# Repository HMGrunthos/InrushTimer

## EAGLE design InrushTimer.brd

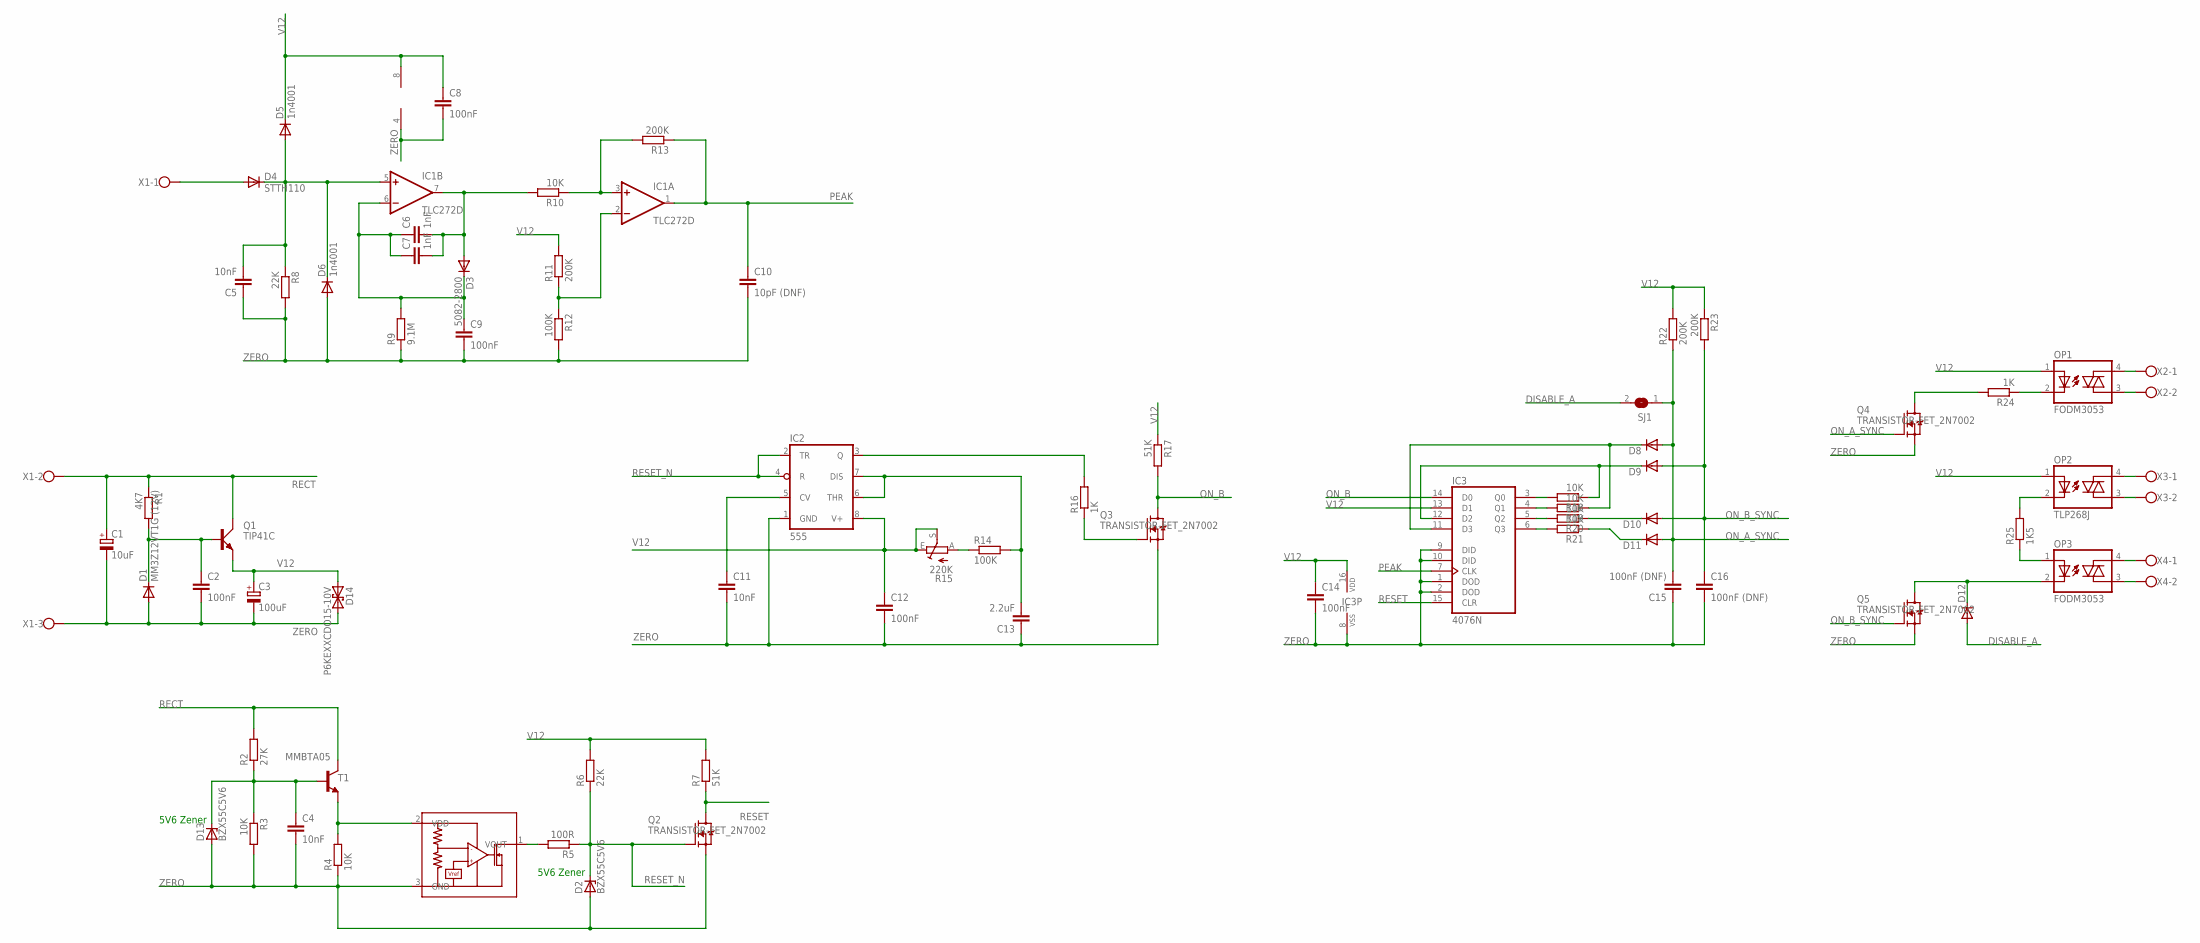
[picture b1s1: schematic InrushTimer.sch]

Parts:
C1: 10uF; E2-5
C2, C12, C14: 100nF; C050-024X044
C3: 100uF; E2,5-7
C4, C11: 10nF; C050-024X044
C5: 10nF; C0805K
C6, C7: 1nF; C0805K
C8: 100nF; C0805
C9: 100nF; C1206K
C10: 10pF (DNF); C0805K
C13: 2.2uF; C1206K
C15, C16: 100nF (DNF); C1206K
D1: MM3Z12VT1G (12V); SOD323-R
D2, D13: BZX55C5V6; DO34Z7
D3: 5082-2800; DO34-7
D4: STTH110; DO41-7.6
D5: 1n4001; DO41-10VN
D6: 1n4001; DO41-7.6
D8: 1N4148DO35-10; DO35-10
D9, D10, D11, D12: 1N4148DO35-7; DO35-7
D14: P6KEXXCDO15-10V; DO15-10V
IC1: TLC272D; SO08
IC2: 555; SO08-555
IC3: 4076N; DIL16
OP1, OP3: FODM3053; FODM
OP2: TLP268J; TLP26*
Q1: TIP41C; TO220AV
Q2, Q3, Q4, Q5: TRANSISTOR-FET_2N7002; TRANSISTOR-FET_SOT23
R1: 4K7; 0207/2V
R2: 27K; 0207/7
R3: 10K; 0207/2V
R4, R18, R19, R20, R21: 10K; R0805
R5: 100R; 0207/7
R6, R8: 22K; 0207/2V
R7, R17: 51K; 0207/2V
R9: 9.1M; 0207/7
R10: 10K; 0207/10
R11, R13, R22: 200K; 0207/2V
R12, R14: 100K; 0207/2V
R15: 220K; CA6H
R16: 1K; R0402
R23: 200K; 0207/7
R24: 1K; 0207/7
R25: 1K5; 0207/2V
SJ1: SJ
T1: MMBTA05; SOT23-BEC
U1: ROHM_BY_ELEMENT14_BATCH_1_BU48XXG; ROHM_BY_ELEMENT14_BATCH_1_SOT95P280X125-5N
X1: W237-103
X2, X3, X4: W237-102

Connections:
DISABLE_A: D12.A, SJ1.2
unnamed: D4.A, X1.1
unnamed: R14.1, R15.A
unnamed: IC3.6 (Q3), R21.2
unnamed: OP3.4 (A2), X4.1
unnamed: OP1.3 (A1), X2.2
unnamed: D12.C, OP3.2 (C), Q5.3 (D)
unnamed: C6.2, C7.2, D3.A, IC1.7 (OUT), R10.2
unnamed: C2.1, D1.C, Q1.B, R1.2
unnamed: C6.1, C7.1, C9.1, D3.C, IC1.6 (-IN), R9.2
unnamed: OP1.4 (A2), X2.1
unnamed: C5.2, D4.C, D5.A, D6.C, IC1.5 (+IN), R8.1
unnamed: OP3.3 (A1), X4.2
unnamed: R4.2, T1.E, U1.2 (VDD)
unnamed: C4.1, D13.C, R2.1, R3.1, T1.B
unnamed: OP3.1 (A), R25.1
unnamed: D9.C, IC3.12 (D2), R18.1
unnamed: OP2.2 (C), R25.2
unnamed: OP1.2 (C), R24.1
unnamed: IC3.5 (Q2), R20.2
unnamed: OP2.4 (A2), X3.1
unnamed: OP2.3 (A1), X3.2
unnamed: D8.C, IC3.11 (D3), R19.1
unnamed: R5.2, U1.1 (VOUT)
unnamed: D11.C, R21.1
unnamed: IC3.4 (Q1), R19.2
unnamed: IC1.3 (+IN), R10.1, R13.2
unnamed: C13.2, IC2.6 (THR), IC2.7 (DIS), R14.2
unnamed: D10.C, R20.1
unnamed: Q4.3 (D), R24.2
unnamed: IC3.3 (Q0), R18.2
unnamed: Q3.1 (G), R16.1
unnamed: C11.1, IC2.5 (CV)
unnamed: IC2.3 (Q), R16.2
ON_A_SYNC: C15.2, D8.A, D11.A, Q4.1 (G), R22.1, SJ1.1
ON_B: IC3.14 (D0), Q3.3 (D), R17.2
ON_B_SYNC: C16.1, D9.A, D10.A, Q5.1 (G), R23.2
PEAK: C10.1, IC1.1 (OUT), IC3.7 (CLK), R13.1
RECT: C1.+, Q1.C, R1.1, R2.2, T1.C, X1.2
RESET: IC3.15 (CLR), Q2.3 (D), R7.1
RESET_N: D2.C, IC2.2 (TR), IC2.4 (R), Q2.1 (G), R5.1, R6.1
THRESH: IC1.2 (-IN), R11.1, R12.1
V12: C3.+, C8.1, C12.1, C14.1, D5.C, D14.A (1), IC1.8 (V+), IC2.8 (V+), IC3.13 (D1), IC3.16 (VDD), OP1.1 (A), OP2.1 (A), Q1.E, R6.2, R7.2, R11.2, R15.E, R15.S, R17.1, R22.2, R23.1
ZERO: C1.-, C2.2, C3.-, C4.2, C5.1, C8.2, C9.2, C10.2, C11.2, C12.2, C13.1, C14.2, C15.1, C16.2, D1.A, D2.A, D6.A, D13.A, D14.C (2), IC1.4 (V-), IC2.1 (GND), IC3.1 (DOD), IC3.2 (DOD), IC3.8 (VSS), IC3.9 (DID), IC3.10 (DID), Q2.2 (S), Q3.2 (S), Q4.2 (S), Q5.2 (S), R3.2, R4.1, R8.2, R9.1, R12.2, U1.3 (GND), X1.3

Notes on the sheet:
5V6 Zener

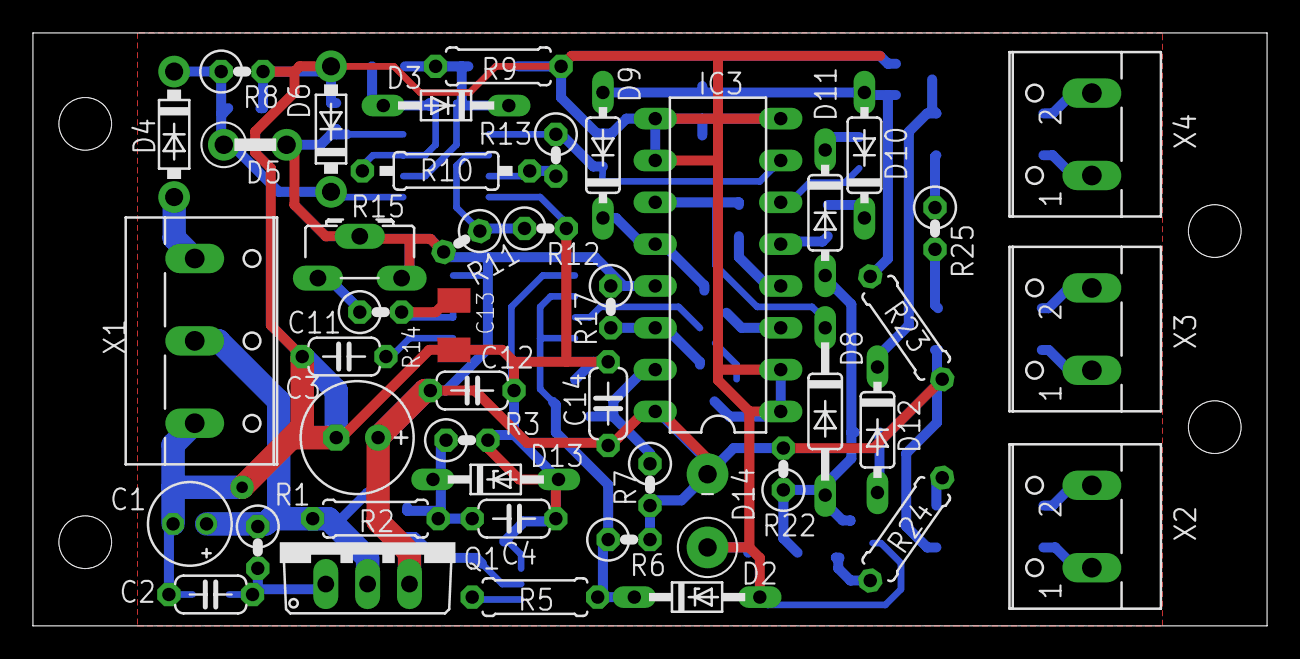
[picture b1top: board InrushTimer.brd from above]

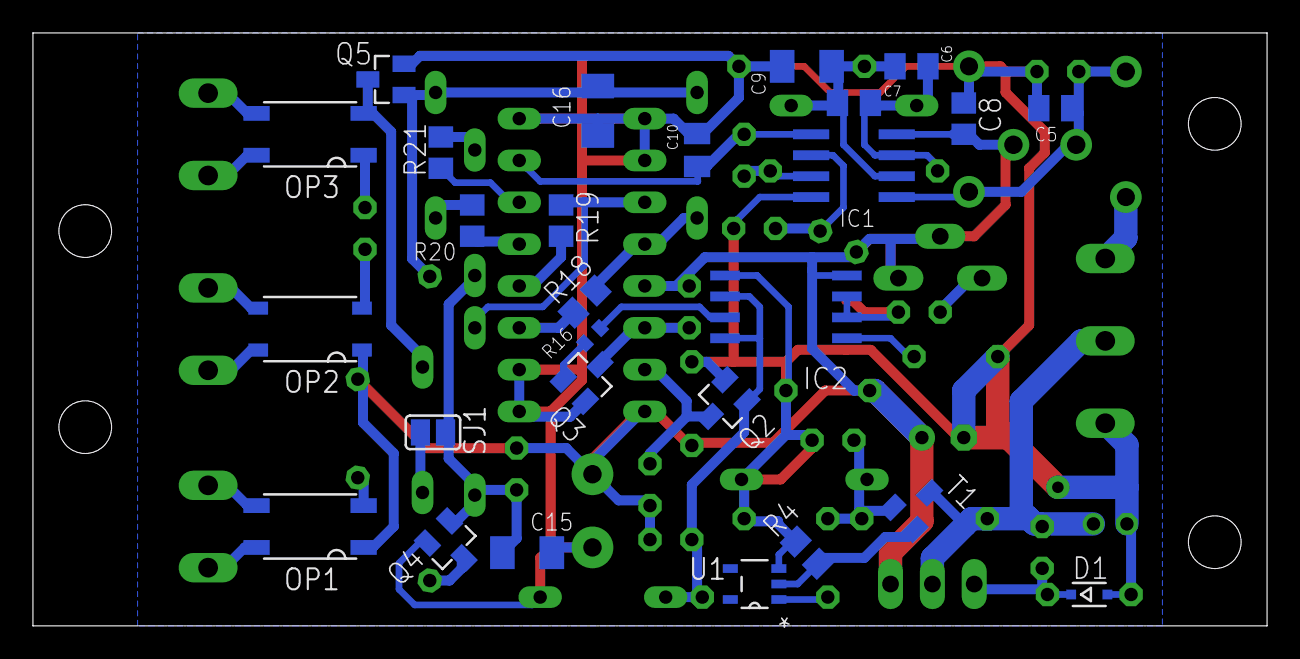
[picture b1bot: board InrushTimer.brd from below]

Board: 2 copper layers, 74.9 x 36.0 mm, 72 parts (27 on the bottom side), 44 nets.

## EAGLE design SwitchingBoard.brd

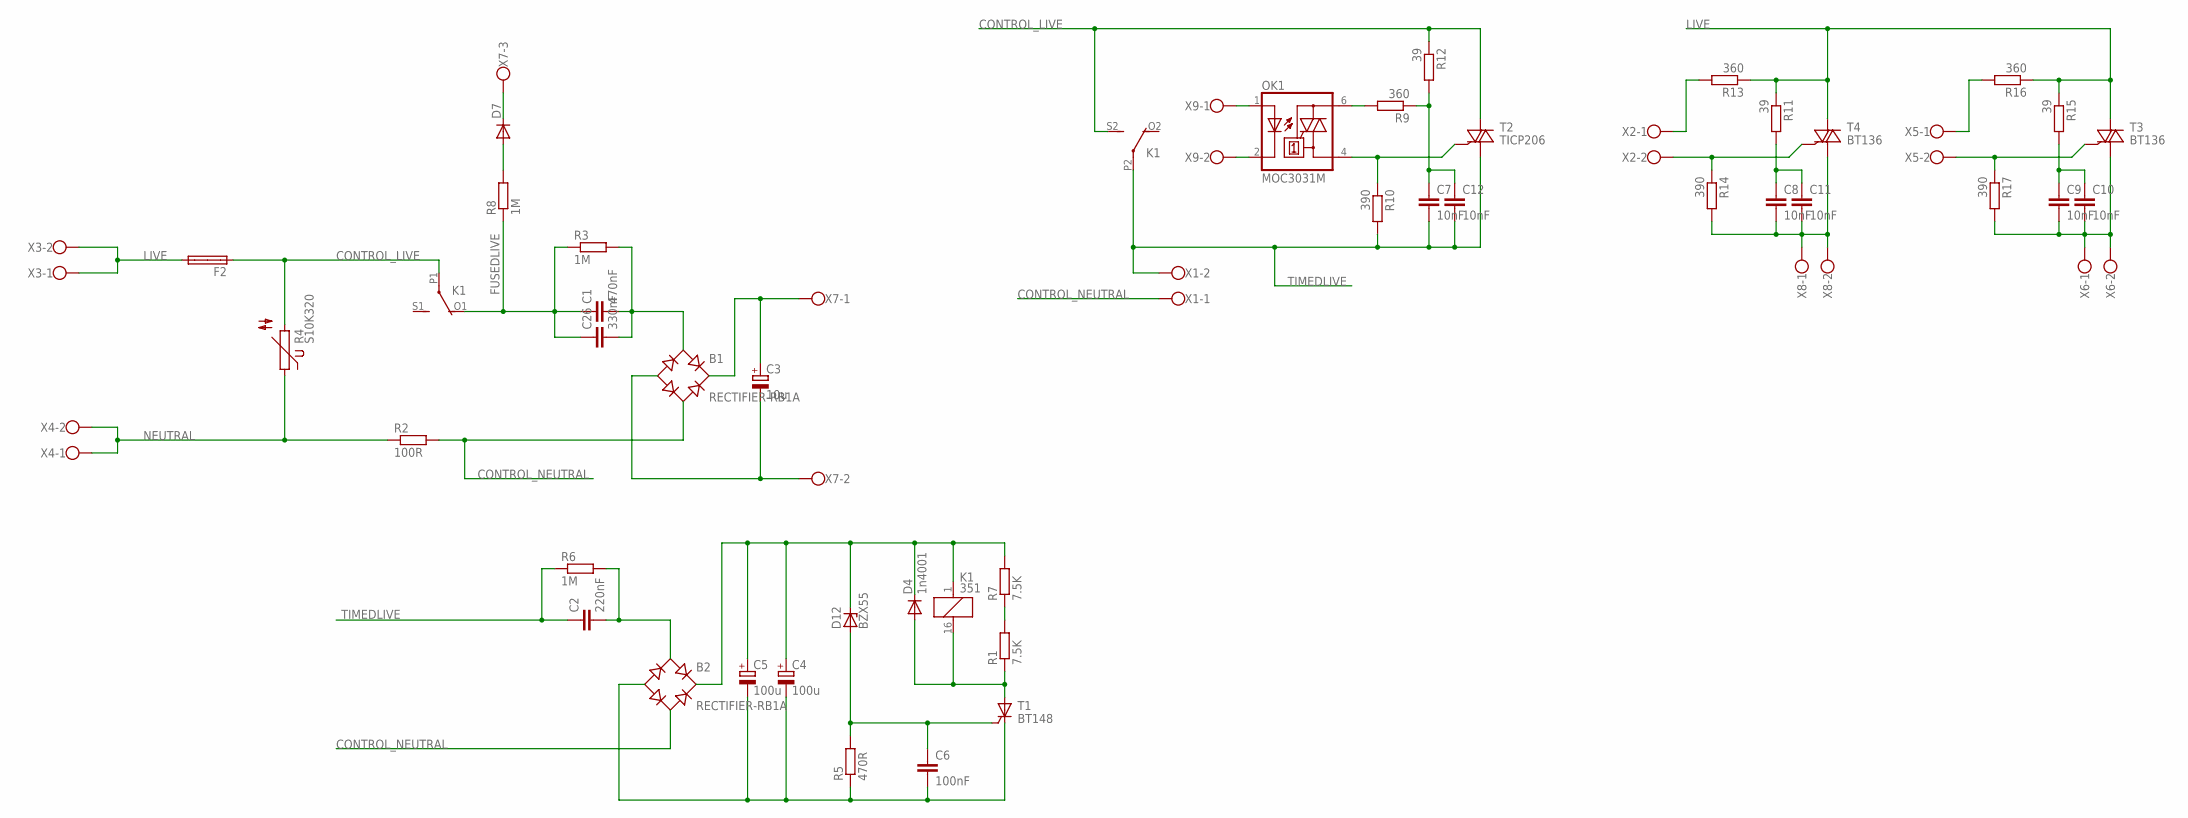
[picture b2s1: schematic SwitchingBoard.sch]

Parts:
B1, B2: RECTIFIER-RB1A; RB1A
C1: 470nF; C225-108X268
C2: 220nF; C225-062X268
C3: 10u; E2-5
C4, C5: 100u; E2,5-7
C6: 100nF; C050-024X044
C7, C8, C9: 10nF; C150-054X183
C10, C11, C12: 10nF; C102-043X133
C26: 330nF; C150-091X182
D4: 1n4001; DO41-10
D7: DIODE-DO41-10; DO41-10
D12: BZX55; DO35Z10
F2: SHKOG
K1: 351
OK1: MOC3031M; DIL06
R1, R7: 7.5K; 0207/7
R2: 100R; 0617/22
R3, R6, R8: 1M; 0617/22
R4: S10K320
R5: 470R; 0207/7
R9, R13, R16: 360; 0207/7
R10, R14, R17: 390; 0207/7
R11, R12, R15: 39; 0207/7
T1: BT148; SOT82S
T2: TICP206; TO92-6
T3, T4: BT136; TO220AB
X1, X2, X3, X4, X5, X6, X8, X9: W237-102
X7: W237-103

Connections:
CONTROL_LIVE: F2.1A, K1.P1, K1.S2 (S), R4.2, R12.1, T2.A2
CONTROL_NEUTRAL: B1.AC2, B2.AC2, R2.2, X1.1
FUSEDLIVE: C1.1, C26.1, K1.O1 (O), R3.1, R8.1
LIVE: F2.2A, R11.1, R13.1, R15.1, R16.1, T3.2 (A2), T4.2 (A2), X3.1, X3.2
unnamed: D7.A, R8.2
unnamed: B2.AC1, C2.2, R6.2
unnamed: R1.2, R7.1
unnamed: B1.AC1, C1.2, C26.2, R3.2
unnamed: D7.C, X7.3
unnamed: D4.A, K1.16 (2), R1.1, T1.A
unnamed: C6.1, D12.A, R5.2, T1.G
unnamed: C8.2, C11.2, R14.2, T4.1 (A1), X8.1, X8.2
unnamed: OK1.6 (A2), R9.2
unnamed: OK1.1 (A), X9.1
unnamed: C9.2, C10.2, R17.2, T3.1 (A1), X6.1, X6.2
unnamed: OK1.2 (C), X9.2
unnamed: OK1.4 (A1), R10.1, T2.G
unnamed: C7.1, C12.1, R9.1, R12.2
unnamed: R13.2, X2.1
unnamed: C8.1, C11.1, R11.2
unnamed: R14.1, T4.3 (G), X2.2
unnamed: C9.1, C10.1, R15.2
unnamed: R16.2, X5.1
unnamed: R17.1, T3.3 (G), X5.2
NEUTRAL: R2.1, R4.1, X4.1, X4.2
RECT: B1.+, C3.+, X7.1
RECTRELAY: B2.+, C4.+, C5.+, D4.C, D12.C, K1.1, R7.2
TIMEDLIVE: C2.1, C7.2, C12.2, K1.P2, R6.1, R10.2, T2.A1, X1.2
ZERO: B1.-, C3.-, X7.2
ZERO1: B2.-, C4.-, C5.-, C6.2, R5.1, T1.C

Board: 2 copper layers, 51 parts (0 on the bottom side), 30 nets, no tracks yet.

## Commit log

2018-07-06 Adding all inrush timer design files and libraries
2018-07-11 Added peak detector opamps
2018-07-13 Still playing with 555 design, peak detector clock seems OK
2018-07-19 Finalised the peak detector, reworked the 555 trigger section.
2018-07-23 Timing flipflops nearly completed
2018-08-28 Updating prior to PCB layout
2018-08-28 Added 3.6V zenner
2022-04-25 Tweaked design and updated component footprints
2022-04-28 Adding relay delay module and updates to inrush timer.
2022-04-28 Updating with inrush model and chenges to cap values to support additional triac channel
2022-04-30 Committing first cut of the board design. Two control signals unrouted.
2022-05-01 Updated some component values and squished the timers further to the right.
2022-05-01 Initial version of routed PCB. All traces routed and passes cursory DRC.
2022-05-01 Tweaked layout to meet more exacting design rules.
2022-05-01 Fixed missing track. Tweaked track widths.
2022-05-01 Adding artwork file.
2022-05-01 Adding script to combine PDFs from quadrants (to save on transparencies)
2022-05-01 Fixed an incorred footprint.
2022-05-01 Updated artwork.
2022-05-02 Tidied up some traces and improved trace seraration.
2022-05-03 Trace adjustments.
2022-05-03 Added artwork for the stop mask
2022-05-04 Adding switching board design.
2022-05-04 Updated schematics and parts for the switching board.
2022-05-05 Checking in first version of the switching board layed out in KiCad
2022-05-05 KiCad switching board schematic passes initial ERC.
2022-05-05 Assigned footprints
2022-05-05 Initial grouping of components on PCB
2022-05-07 Tweaked layout based on autorouter run.
2022-05-07 Updated artwork
2022-05-07 Updated schematics and board to address error in aux output assignment.
2022-05-12 Committing changes to circuit to remove a time and put the optoisolators into series.
2022-05-12 Fixed reset generator.
2022-05-12 Simplified resistive divider setup.
2022-05-13 Updated model and board with circuit and component values.
2022-05-13 Changed gate resistors and checked component values.
2022-05-13 Added inductor model and tweaked schematic.
2022-05-14 Fixed inverted comparator and actually calculated hysteresis resistors!
2022-05-14 Updated values and topology on schematic.
2022-05-14 Corrected component values (units)
2022-05-14 Tidied up model schematic.
2022-05-14 Updated optotriac symbol
2022-05-14 Fixed missing libraries by moving parts into local lib. Renumbered components.
2022-05-14 Updated component packages
2022-05-14 Updated zener model and added annotation on schematic.
2022-05-15 Added measurements for peak clock rise and fall time. Tidied up library imports. Sorted out gate capacitance on output of comparator.
2022-05-15 Tweaked convergence option and changed zenner follower to ZTX451
2022-05-15 Removed ||'ll resistance for looking at peak voltage. Removed unused models.
2022-05-15 Re-layed out peak detector, supply and reset generator.
2022-05-15 Layout changes.
2022-05-16 Removed optocoupler from this board and updated the fuseholder footprint.
2022-05-17 ayed out the timer - starting on the D types. Fixed incorrect gate capacitance.
2022-05-17 Added custom fuse footprint and updated PCB.
2022-05-17 Refitted the timer and pulse generator.
2022-05-17 Everything on the board - not routed.
2022-05-17 Added a couple more power routes.
2022-05-18 First complete routing fit. Passes design rules.
2022-05-18 Slight track style tweaks.
2022-05-20 Pushed some tracks to the bottom side
2022-05-20 Adjusted resistor value
2022-05-20 Shifted component to the bottom layer and adjusted some track placements.
2022-05-20 Track and component positions.
2022-05-20 Tidied up component and track placement.
2022-05-20 Rev two layout - minor change to track angle
2022-05-20 Rev two masks
2022-05-23 Added photo of PCB processing notes.
2022-05-25 Changed pass element to TIP41C and moved some components around to make more space.
2022-05-25 Rerouted power supply section and made some space around the pot.
2022-05-25 Fixed some component orientations.
2022-05-26 Tweaked ground and component positions - still to do; adjust pad sizes.
2022-05-27 Increased TH pad sizes and adjusted component positions to pass DRC.
2022-05-27 Adding updated artwork.
2022-05-29 Tweaked track position.
2022-06-01 Playing with layout and routing in KiCad
2022-06-03 Shuffled component placement to avoid via.
2022-06-03 Fixed TRIAC symbol and tweaked layout further.
2022-08-25 Added duplicated resistors to hit worst case voltage ratings.
2022-10-17 Fixed up silkscreen and added job file from JLCPCB
2022-10-17 More silkscreen fixes.
2022-10-18 Checked in gerber files for inrush timer production.
2022-12-14 Fixed schematic connections.
2024-02-17 Added missing diode model
2024-02-17 Attempt to fix a reported issue with the diode syntax in pspice.
